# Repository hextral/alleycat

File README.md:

# alleycat

---

alley cat

---

features!

- wireless
- split
- oled support
- triple encoder support (4 without joystick)
- 3ds joystick nip
- optional fn row

---

specifications!

- firmware is zmk
- uses nRF52840 in the E73-2G4M08S1C package

---

layout!

\
 \
  \
   \
    \

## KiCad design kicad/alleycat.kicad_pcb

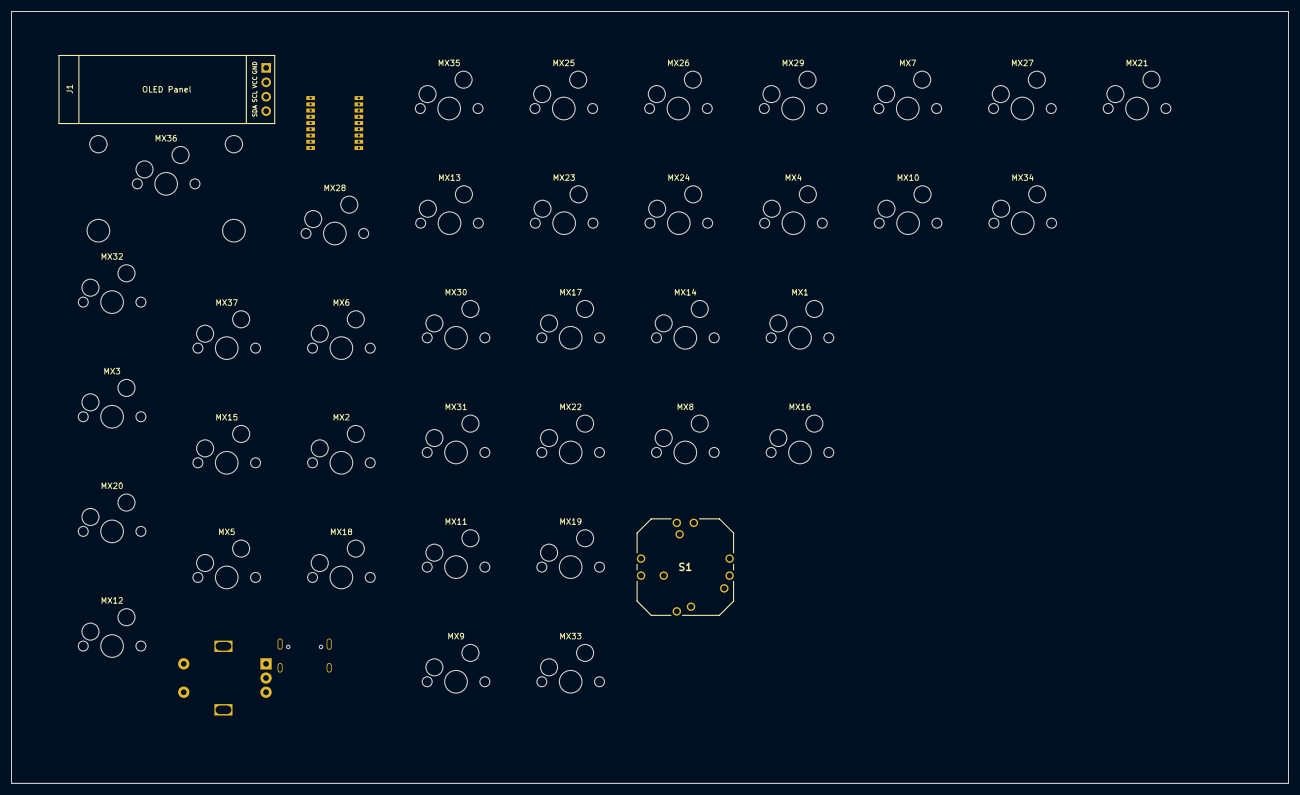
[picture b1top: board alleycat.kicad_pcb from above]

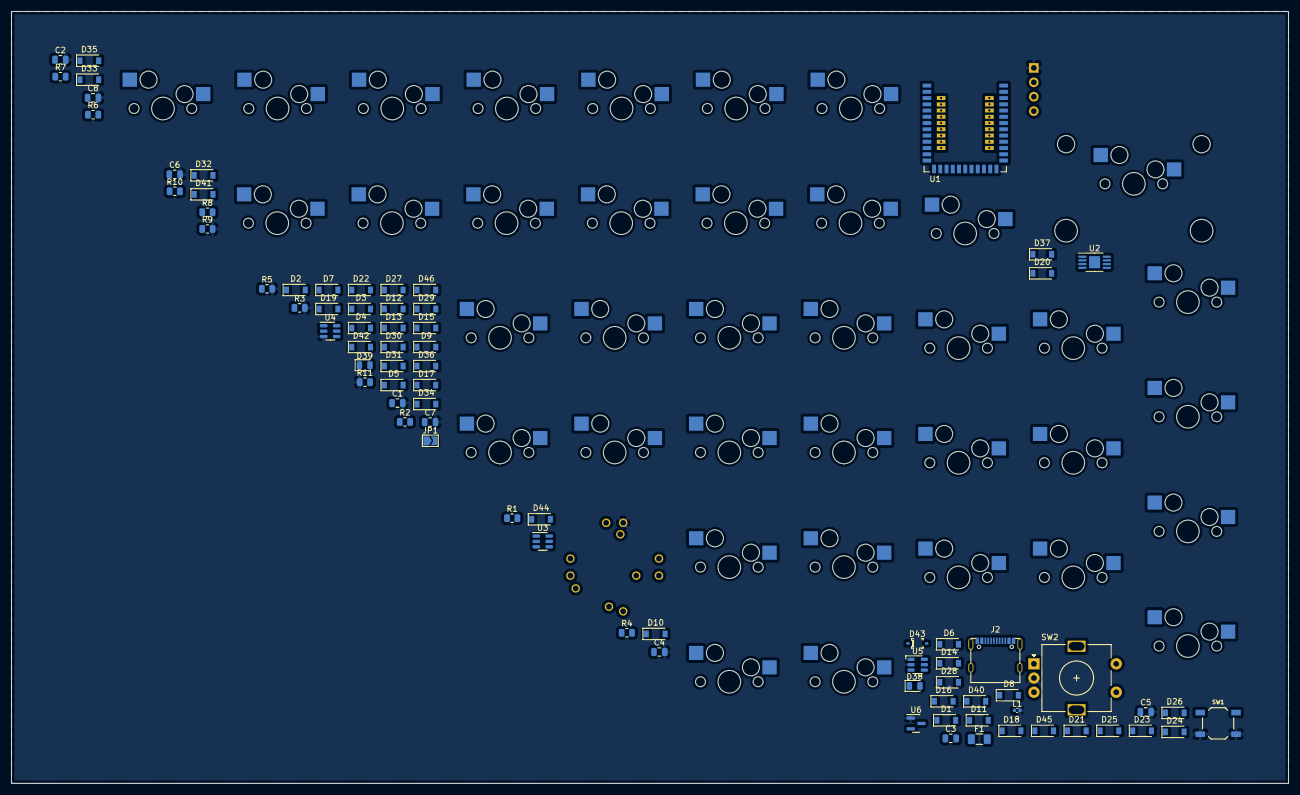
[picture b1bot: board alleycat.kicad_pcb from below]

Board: 2 copper layers, 225.0 x 136.0 mm, 116 parts (77 on the bottom side), 77 nets, no tracks yet.

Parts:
C1: 10uf; C_0805_2012Metric
C2, C3, C8: 100nf; C_0805_2012Metric
C4, C5: 4.7uf; C_0805_2012Metric
C6, C7: 1uf; C_0805_2012Metric
D1, D2, D3, D4, D5, D6, D7, D8, D9, D10, D11, D12, D13, D14, D15, D16, D17, D18, D19, D20, D21, D22, D23, D24, D25, D26, D27, D28, D29, D30, D31, D32, D33, D34, D35, D36, D37, D40, D41, D42, D44, D45, D46: D_Small; D_SOD-123
D38, D39: LED; LED_0805_2012Metric
D43: D_TVS; SOD-323
F1: Polyfuse_Small; Fuse_1206_3216Metric
J1: Conn_01x04_Male; SSD1306-0.91-OLED-4pin-128x32
J2: USB_C_Receptacle_USB2.0; TYPE-C-31-M-12
JP1: THERM; SolderJumper-2_P1.3mm_Open_TrianglePad1.0x1.5mm
L1: L; C_0402_1005Metric
MX1, MX2, MX3, MX4, MX5, MX6, MX7, MX8, MX9, MX10, MX11, MX12, MX13, MX14, MX15, MX16, MX17, MX18, MX19, MX20, MX21, MX22, MX23, MX24, MX25, MX26, MX27, MX28, MX29, MX30, MX31, MX32, MX33, MX34, MX35, MX37: MX-NoLED; MXOnly-1U-Hotswap
MX36: MX-NoLED; MXOnly-2U-Hotswap
R1, R2: 2.7k; R_0805_2012Metric
R3: 1.8k; R_0805_2012Metric
R4: 3.3k; R_0805_2012Metric
R5: 22k; R_0805_2012Metric
R6, R7: 5.1k; R_0805_2012Metric
R8: 100; R_0805_2012Metric
R9: 1k; R_0805_2012Metric
R10: 806k; R_0805_2012Metric
R11: 2M; R_0805_2012Metric
S1: RKJXT1F42001
SW1: SW_Push; SW_SPST_TL3342
SW2: RotaryEncoder_Switch; RotaryEncoder_Alps_EC11E-Switch_Vertical_H20mm
U1: nRF52840_holyiot_18010
U2: TP4056; MSOP-8-1EP_3x3mm_P0.65mm_EP1.95x2.15mm
U3: DW01A; SOT-23-6
U4: FS8205; SOT-23-6
U5: SRV05-4; SOT-23-6-routable
U6: XC6206PxxxMR; SOT-23

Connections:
+3.3V: C7.1, C8.1, U1.14 (VDD_nRF), U6.2 (VO)
+5V: C1.1, C2.1, D38.2 (A), D39.2 (A), F1.2, J1.2, R4.1, U2.4 (VCC), U5.5 (VP)
BAT+: C4.1, C5.1, C6.1, R8.1, R10.2, U2.5 (BAT), U6.3 (VI)
BAT-: C3.2, U3.6 (VSS), U4.1 (S1)
D+: J2.A6 (D+), J2.B6 (D+), U5.1 (IO1)
D-: J2.A7 (D-), J2.B7 (D-), U5.3 (IO2)
GND: C1.2, C2.2, C4.2, C5.2, C6.2, C7.2, C8.2, J1.1, JP1.1 (A), L1.2, R3.2, R5.2, R9.2, R11.1, S1.8 (ENCODER_COM), SW1.2, SW2.C, U2.3 (GND), U4.3 (S2), U5.2 (VN), U6.1 (GND)
GNDPWR: L1.1, R6.2, R7.1
unnamed: C3.1, R8.2, U3.5 (VDD)
unnamed: D1.2 (A), MX1.2 (ROW)
unnamed: D2.2 (A), MX2.2 (ROW)
unnamed: D3.2 (A), MX3.2 (ROW)
unnamed: D4.2 (A), MX4.2 (ROW)
unnamed: D5.2 (A), MX5.2 (ROW)
unnamed: D6.2 (A), MX6.2 (ROW)
unnamed: D7.2 (A), MX7.2 (ROW)
unnamed: D8.2 (A), MX8.2 (ROW)
unnamed: D9.2 (A), MX9.2 (ROW)
unnamed: D10.2 (A), MX10.2 (ROW)
unnamed: D11.2 (A), MX11.2 (ROW)
unnamed: D12.2 (A), MX12.2 (ROW)
unnamed: D13.2 (A), MX13.2 (ROW)
unnamed: D14.2 (A), MX14.2 (ROW)
unnamed: D15.2 (A), MX15.2 (ROW)
unnamed: D16.2 (A), MX16.2 (ROW)
unnamed: D17.2 (A), MX17.2 (ROW)
unnamed: D18.2 (A), MX18.2 (ROW)
unnamed: D19.2 (A), MX19.2 (ROW)
unnamed: D20.2 (A), MX20.2 (ROW)
unnamed: D21.2 (A), MX21.2 (ROW)
unnamed: D22.2 (A), MX22.2 (ROW)
unnamed: D23.2 (A), MX23.2 (ROW)
unnamed: D24.2 (A), MX24.2 (ROW)
unnamed: D25.2 (A), MX25.2 (ROW)
unnamed: D26.2 (A), MX26.2 (ROW)
unnamed: D27.2 (A), MX27.2 (ROW)
unnamed: D28.2 (A), MX28.2 (ROW)
unnamed: D29.2 (A), MX29.2 (ROW)
unnamed: D30.2 (A), MX30.2 (ROW)
unnamed: D31.2 (A), MX31.2 (ROW)
unnamed: D32.2 (A), MX32.2 (ROW)
unnamed: D33.2 (A), MX33.2 (ROW)
unnamed: D34.2 (A), MX34.2 (ROW)
unnamed: D35.2 (A), MX35.2 (ROW)
unnamed: D36.2 (A), MX36.2 (ROW)
unnamed: D37.2 (A), MX37.2 (ROW)
unnamed: D38.1 (K), R1.2
unnamed: D39.1 (K), R2.2
unnamed: D40.2 (A), S1.1 (A)
unnamed: D41.2 (A), S1.4 (B)
unnamed: D42.2 (A), S1.6 (C)
unnamed: D44.2 (A), SW2.S2
unnamed: D45.2 (A), S1.7 (COM)
unnamed: D46.2 (A), S1.9 (D_1)
unnamed: J2.A5 (CC1), R6.1
unnamed: JP1.2 (B), R4.2, R5.1, U2.1 (TEMP)
unnamed: R2.1, U2.6 (STDBY)
unnamed: R3.1, U2.2 (PROG)
unnamed: R9.1, U3.2 (CSI)
unnamed: U3.1 (OD), U4.6 (G1)
unnamed: U3.3 (OC), U4.4 (G2)
VBUS: F1.1, J2.B4 (VBUS)
VSENSE: R10.1, R11.2, U1.11 (P0.31)
col_0: MX1.1 (COL), MX2.1 (COL), MX3.1 (COL), MX4.1 (COL), MX5.1 (COL), MX6.1 (COL)
col_1: MX7.1 (COL), MX8.1 (COL), MX9.1 (COL), MX10.1 (COL), MX11.1 (COL), MX12.1 (COL)
col_2: MX13.1 (COL), MX14.1 (COL), MX15.1 (COL), MX16.1 (COL), MX17.1 (COL), MX18.1 (COL)
col_3: MX19.1 (COL), MX20.1 (COL), MX21.1 (COL), MX22.1 (COL), MX23.1 (COL), MX24.1 (COL)
col_4: MX25.1 (COL), MX26.1 (COL), MX27.1 (COL), MX28.1 (COL), MX29.1 (COL), MX30.1 (COL)
col_5: MX31.1 (COL), MX32.1 (COL), MX33.1 (COL), MX34.1 (COL), MX35.1 (COL), MX36.1 (COL)
col_6: MX37.1 (COL), S1.2 (PUSH), S1.3 (GND_TERMINAL)
reset: SW1.1, U1.21 (P0.18/RESET)
row_0: D6.1 (K), D12.1 (K), D18.1 (K), D24.1 (K), D30.1 (K), D36.1 (K), D40.1 (K), D44.1 (K)
row_1: D5.1 (K), D11.1 (K), D17.1 (K), D23.1 (K), D29.1 (K), D35.1 (K), D41.1 (K)
row_2: D4.1 (K), D10.1 (K), D16.1 (K), D22.1 (K), D28.1 (K), D34.1 (K), D42.1 (K)
row_3: D3.1 (K), D9.1 (K), D15.1 (K), D21.1 (K), D27.1 (K), D33.1 (K), D46.1 (K)
row_4: D2.1 (K), D8.1 (K), D14.1 (K), D20.1 (K), D26.1 (K), D32.1 (K), D45.1 (K)
row_5: D1.1 (K), D7.1 (K), D13.1 (K), D19.1 (K), D25.1 (K), D31.1 (K), D37.1 (K)

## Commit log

2022-09-02 init
2022-09-02 added outline
2022-09-03 made schematic bigger
2022-09-03 wicked testy stuff yknow
2022-09-03 hot swappy :)
2022-09-03 for mat
2022-09-04 modified schematic
2022-09-04 schematic edits
2022-09-04 cogchamp
2022-09-04 better outline
2022-09-04 added footprints, and added to schematic
2022-09-05 added the rest of the schematic stuff
2022-09-05 wicked
2022-09-05 fuck cache
2022-09-06 WICKED BASED NEW LAYOUT POGGERS
2022-09-06 do it for the left side too
2022-09-07 re add main project file
2022-09-07 ANY ALIGNERS?
2022-09-07 wicked usb
2022-09-07 pogchamp
2022-09-07 new library dropped
2022-09-07 battery management
2022-09-07 wicked voltage regulator
2022-09-07 uhh uhhh uhhh uhh uhhh uhhh uhhh uuhhh uhhh uhh uhh uhhhu hh uhh footprints
2022-09-07 diod
2022-09-07 alt right
2022-09-08 nyaaaa
2022-09-08 fuck them backups
2022-09-08 rows :)
2022-09-08 fuck them backups part 2
2022-09-08 did a little pcbing
2022-09-08 fuck them backups part 3
2022-09-08 cols
2022-09-08 wicked cols
2022-09-08 keebio peepoGlad
2022-09-08 uhh wicked
2022-09-08 pcb edit pog pog pog
2022-09-08 swag
2022-09-08 schematic hook
2022-09-11 blendy
2022-09-11 large
2022-09-11 blend/the keyboard.blend: convert to Git LFS
2022-09-13 pogged
2022-09-14 changed 3d models
2022-09-15 did the right allignment
2022-09-15 right side check
2022-09-15 changed io protector pin so it isnt stupid
